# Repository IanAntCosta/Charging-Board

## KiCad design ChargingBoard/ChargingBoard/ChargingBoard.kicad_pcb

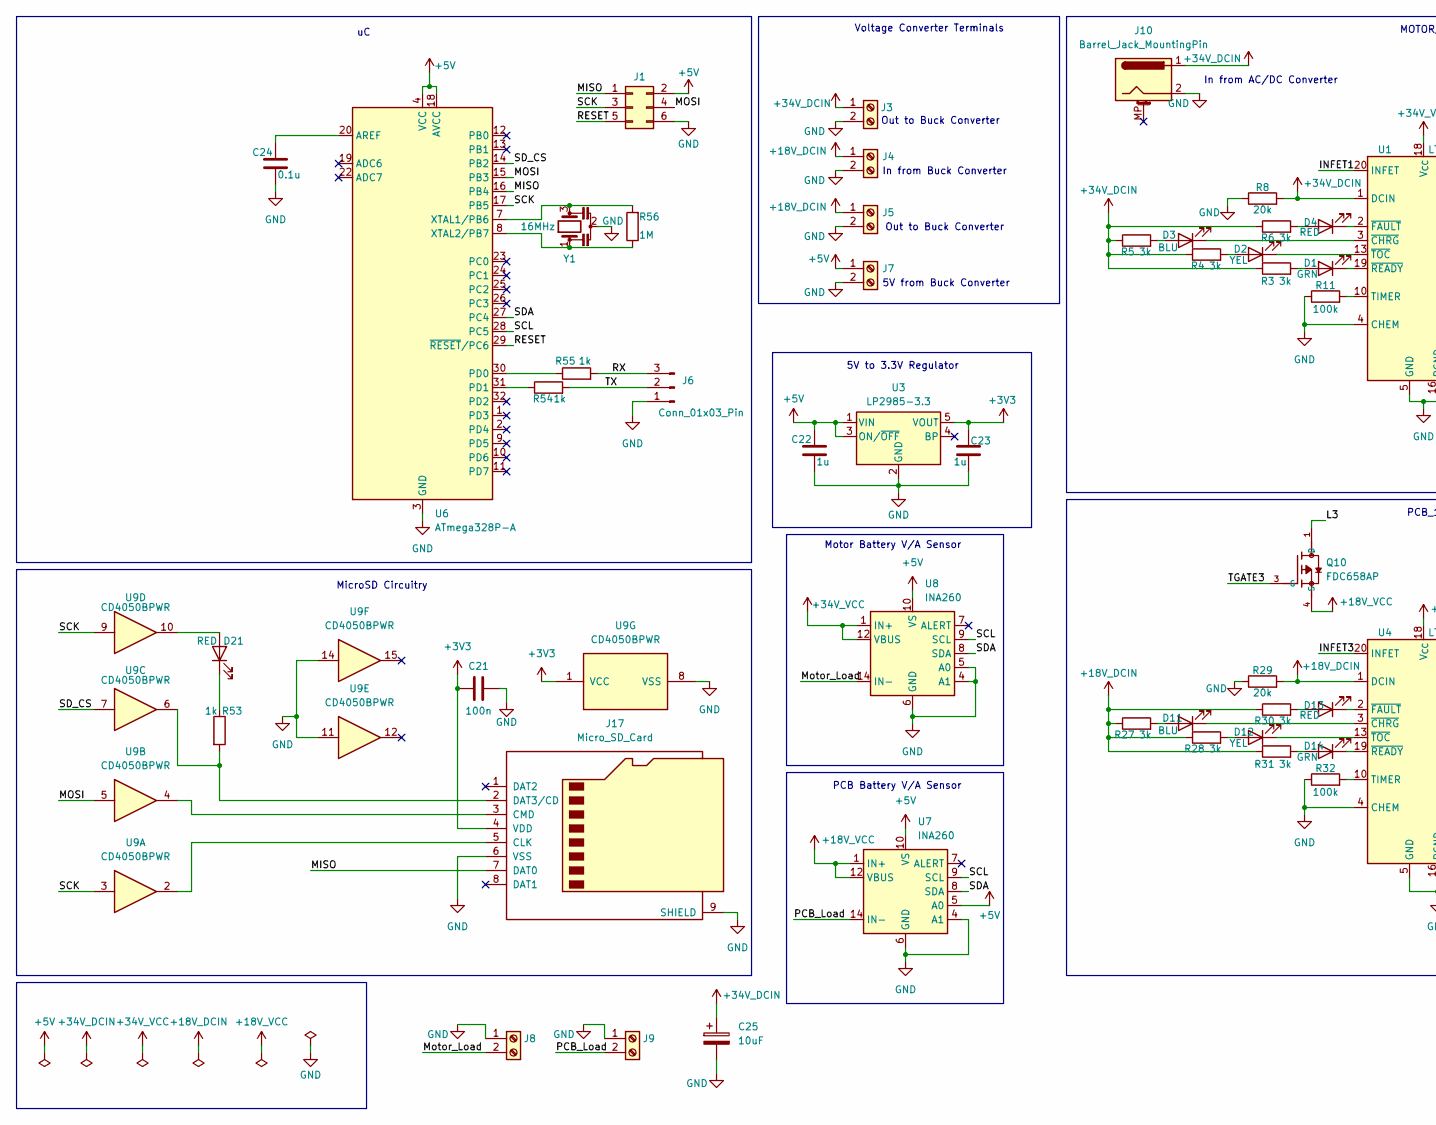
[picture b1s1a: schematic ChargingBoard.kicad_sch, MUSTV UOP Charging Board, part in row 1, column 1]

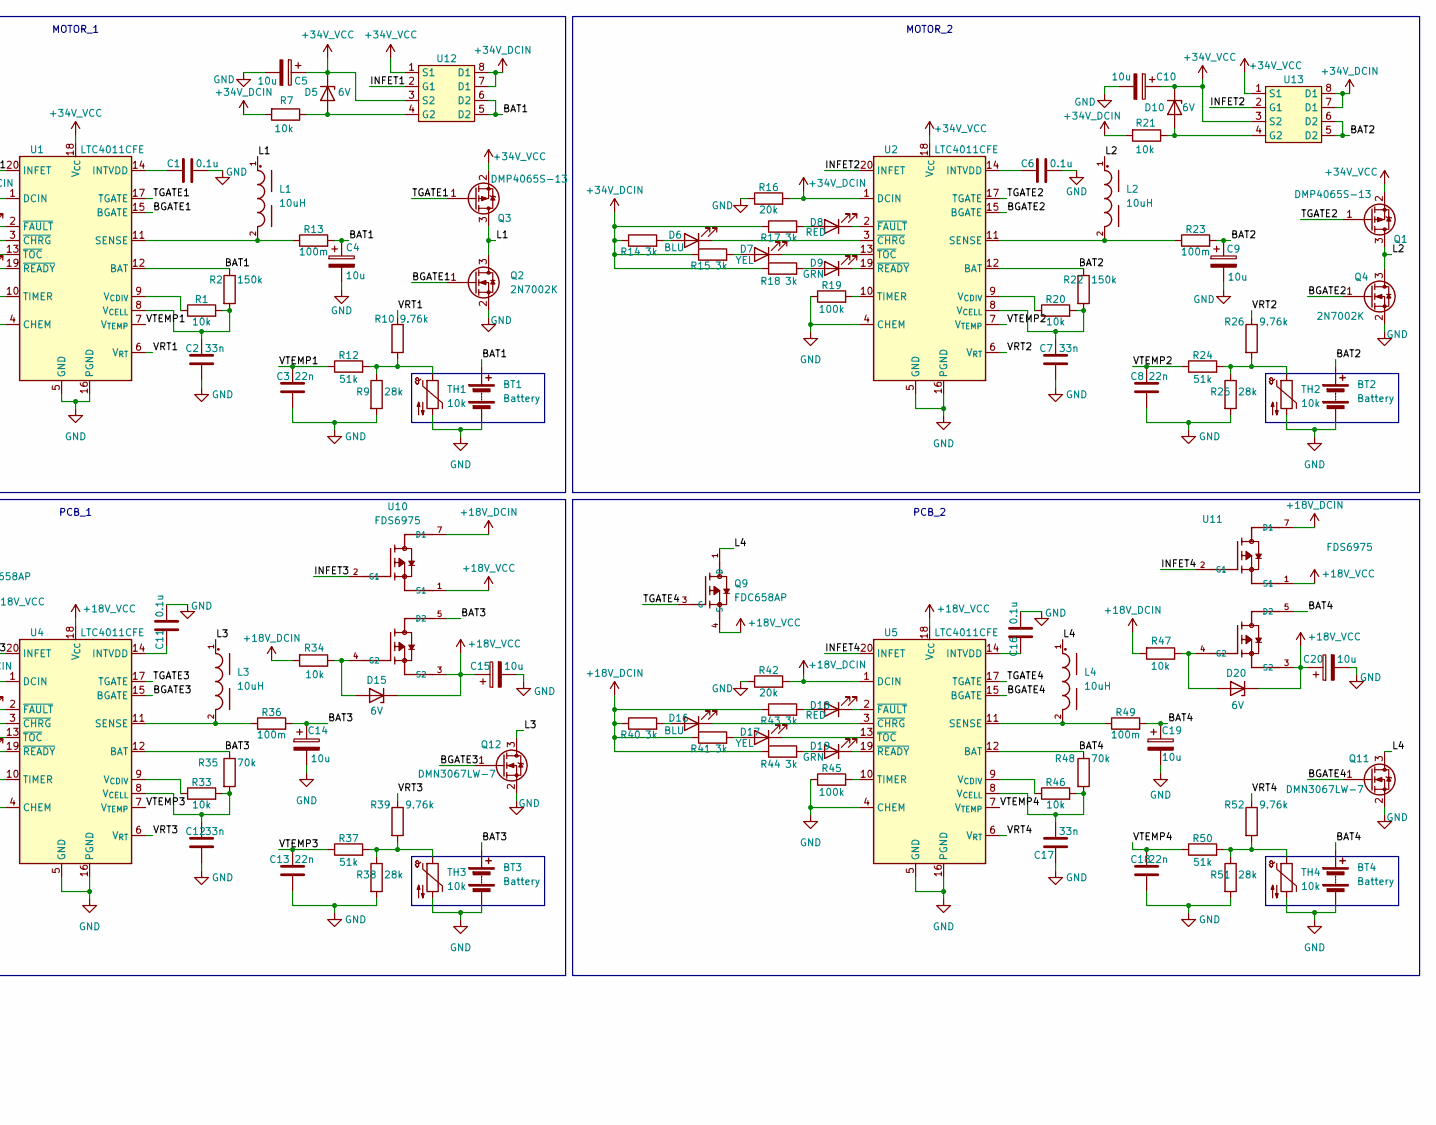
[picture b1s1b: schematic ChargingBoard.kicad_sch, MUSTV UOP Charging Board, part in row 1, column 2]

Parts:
BT1, BT2, BT3, BT4: Battery; TerminalBlock_Phoenix_MPT-0,5-2-2.54_1x02_P2.54mm_Horizontal
C1, C6, C11, C16, C24: 0.1u; C_0603_1608Metric_Pad1.08x0.95mm_HandSolder
C2, C7, C12, C17: 33n; C_0603_1608Metric_Pad1.08x0.95mm_HandSolder
C3, C8, C13, C18: 22n; C_0603_1608Metric_Pad1.08x0.95mm_HandSolder
C4, C5, C9, C10, C14, C15, C19, C20: 10u; CP_Radial_D5.0mm_P2.00mm
C21: 100n; C_0603_1608Metric_Pad1.08x0.95mm_HandSolder
C22, C23: 1u; C_0603_1608Metric_Pad1.08x0.95mm_HandSolder
C25: 10uF; CP_Axial_L10.0mm_D4.5mm_P15.00mm_Horizontal
D1, D9, D14, D19: GRN; LED_0603_1608Metric_Pad1.05x0.95mm_HandSolder
D2, D7, D12, D17: YEL; LED_0603_1608Metric_Pad1.05x0.95mm_HandSolder
D3, D6, D11, D16: BLU; LED_0603_1608Metric_Pad1.05x0.95mm_HandSolder
D4, D8, D13, D18, D21: RED; LED_0603_1608Metric_Pad1.05x0.95mm_HandSolder
D5, D10: 6V; D_SOD-123F
D15, D20: 6V; D_SOD-323_HandSoldering
J1: Conn_02x03_Odd_Even; PinSocket_2x03_P2.54mm_Vertical
J3, J4, J5, J7, J8, J9: Screw_Terminal_01x02; TerminalBlock_Phoenix_MKDS-1-2-3.81_1x02_P3.81mm_Horizontal
J6: Conn_01x03_Pin; PinHeader_1x03_P2.54mm_Vertical
J10: Barrel_Jack_MountingPin; BarrelJack_GCT_DCJ200-10-A_Horizontal
J17: Micro_SD_Card; microSD_HC_Hirose_DM3BT-DSF-PEJS
L1, L2, L3, L4: 10uH; WE-LHMI_7050; DigiKey_Part_Number 732-3358-1-ND
Q1, Q3: DMP4065S-13; SOT-23
Q2, Q4: 2N7002K; SOT-23
Q9, Q10: FDC658AP; SuperSOT-6
Q11, Q12: DMN3067LW-7; SOT-323_SC-70
R1, R7, R20, R21, R33, R34, R46, R47: 10k; R_0603_1608Metric_Pad0.98x0.95mm_HandSolder
R2, R22: 150k; R_0603_1608Metric_Pad0.98x0.95mm_HandSolder
R3, R4, R5, R6, R14, R15, R17, R18, R27, R28, R30, R31, R40, R41, R43, R44: 3k; R_0603_1608Metric_Pad0.98x0.95mm_HandSolder
R8, R16, R29, R42: 20k; R_0603_1608Metric_Pad0.98x0.95mm_HandSolder
R9, R25, R38, R51: 28k; R_0603_1608Metric_Pad0.98x0.95mm_HandSolder
R10, R26, R39, R52: 9.76k; R_0603_1608Metric_Pad0.98x0.95mm_HandSolder
R11, R19, R32, R45: 100k; R_0603_1608Metric_Pad0.98x0.95mm_HandSolder
R12, R24, R37, R50: 51k; R_0603_1608Metric_Pad0.98x0.95mm_HandSolder
R13, R23, R36, R49: 100m; R_0805_2012Metric_Pad1.20x1.40mm_HandSolder
R35, R48: 70k; R_0603_1608Metric_Pad0.98x0.95mm_HandSolder
R53, R54, R55: 1k; R_0603_1608Metric_Pad0.98x0.95mm_HandSolder
R56: 1M; R_0603_1608Metric_Pad0.98x0.95mm_HandSolder
TH1, TH2, TH3, TH4: 10k; PinHeader_1x02_P2.54mm_Vertical
U1, U2, U4, U5: LTC4011CFE; HTSSOP-20-1EP_4.4x6.5mm_P0.65mm_EP2.74x3.86mm
U3: LP2985-3.3; SOT-23-5
U6: ATmega328P-A; TQFP-32_7x7mm_P0.8mm
U7, U8: INA260; TSSOP-16_4.4x5mm_P0.65mm
U9: CD4050BPWR; SOIC-16_3.9x9.9mm_P1.27mm
U10, U11: FDS6975; SOIC-8_3.9x4.9mm_P1.27mm
U12, U13: Si4909DY-T1-GE3; SOIC-8_3.9x4.9mm_P1.27mm
Y1: 16MHz; Resonator_Murata_DSN6-3Pin_W7.0mm_H2.5mm

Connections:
+3V3: C21.1, C23.1, J17.4 (VDD), U3.5 (VOUT), U9.1 (VCC)
+5V: C22.1, J1.2, J7.1, U3.1 (VIN), U3.3 (ON/~OFF), U6.4 (VCC), U6.6 (VCC), U6.18 (AVCC), U7.5 (A0), U7.10 (VS), U8.10 (VS)
+18V_DCIN: J4.1, J5.1, R27.1, R28.1, R29.2, R30.1, R31.1, R34.2, R40.1, R41.1, R42.2, R43.1, R44.1, R47.2, U4.1 (DCIN), U5.1 (DCIN), U10.7 (D1), U10.8 (D1), U11.7 (D1), U11.8 (D1)
+18V_VCC: C15.1, C20.1, D15.1 (K), D20.1 (K), Q9.4 (S), Q10.4 (S), U4.18 (V_{CC}), U5.18 (V_{CC}), U7.1 (IN+), U7.2 (IN+), U7.3 (IN+), U7.12 (VBUS), U10.1 (S1), U10.3 (S2), U11.1 (S1), U11.3 (S2)
+34V_DCIN: C25.1, J3.1, J10.1, R3.1, R4.1, R5.1, R6.1, R7.2, R8.2, R14.1, R15.1, R16.2, R17.1, R18.1, R21.2, U1.1 (DCIN), U2.1 (DCIN), U12.7 (D1), U12.8 (D1), U13.7 (D1), U13.8 (D1)
+34V_VCC: C5.1, C10.1, D5.1 (K), D10.1 (K), Q1.2 (S), Q3.2 (S), U1.18 (V_{CC}), U2.18 (V_{CC}), U8.1 (IN+), U8.2 (IN+), U8.3 (IN+), U8.12 (VBUS), U12.1 (S1), U12.3 (S2), U13.1 (S1), U13.3 (S2)
/BAT1: BT1.1 (+), C4.1, R2.1, R13.2, U1.12 (BAT), U12.5 (D2), U12.6 (D2)
/BAT2: BT2.1 (+), C9.1, R22.1, R23.2, U2.12 (BAT), U13.5 (D2), U13.6 (D2)
/BAT3: BT3.1 (+), C14.1, R35.1, R36.2, U4.12 (BAT), U10.5 (D2), U10.6 (D2)
/BAT4: BT4.1 (+), C19.1, R48.1, R49.2, U5.12 (BAT), U11.5 (D2), U11.6 (D2)
/BGATE1: Q2.1 (G), U1.15 (BGATE)
/BGATE2: Q4.1 (G), U2.15 (BGATE)
/BGATE3: Q12.1 (G), U4.15 (BGATE)
/BGATE4: Q11.1 (G), U5.15 (BGATE)
/INFET1: U1.20 (INFET), U12.2 (G1)
/INFET2: U2.20 (INFET), U13.2 (G1)
/INFET3: U4.20 (INFET), U10.2 (G1)
/INFET4: U5.20 (INFET), U11.2 (G1)
/L1: L1.1, Q2.3 (D), Q3.3 (D)
/L2: L2.1, Q1.3 (D), Q4.3 (D)
/L3: L3.1, Q10.1 (D), Q10.2 (D), Q10.5 (D), Q10.6 (D), Q12.3 (D)
/L4: L4.1, Q9.1 (D), Q9.2 (D), Q9.5 (D), Q9.6 (D), Q11.3 (D)
/MISO: J1.1, J17.7 (DAT0), U6.16 (PB4)
/MOSI: J1.4, U6.15 (PB3), U9.5
/Motor_Load: J8.2, U8.14 (IN-), U8.15 (IN-), U8.16 (IN-)
/PCB_Load: J9.2, U7.14 (IN-), U7.15 (IN-), U7.16 (IN-)
/RESET: J1.5, U6.29 (~RESET/PC6)
/RX: J6.3, R55.2
/SCK: J1.3, U6.17 (PB5), U9.3, U9.9
/SCL: U6.28 (PC5), U7.9 (SCL), U8.9 (SCL)
/SDA: U6.27 (PC4), U7.8 (SDA), U8.8 (SDA)
/SD_CS: U6.14 (PB2), U9.7
/TGATE1: Q3.1 (G), U1.17 (TGATE)
/TGATE2: Q1.1 (G), U2.17 (TGATE)
/TGATE3: Q10.3 (G), U4.17 (TGATE)
/TGATE4: Q9.3 (G), U5.17 (TGATE)
/TX: J6.2, R54.2
/VRT1: R10.1, U1.6 (V_{RT})
/VRT2: R26.1, U2.6 (V_{RT})
/VRT3: R39.1, U4.6 (V_{RT})
/VRT4: R52.1, U5.6 (V_{RT})
/VTEMP1: C3.1, R12.1, U1.7 (V_{TEMP})
/VTEMP2: C8.1, R24.1, U2.7 (V_{TEMP})
/VTEMP3: C13.1, R37.1, U4.7 (V_{TEMP})
/VTEMP4: C18.1, R50.1, U5.7 (V_{TEMP})
GND: BT1.2 (-), BT2.2 (-), BT3.2 (-), BT4.2 (-), C1.2, C2.2, C3.2, C4.2, C5.2, C6.2, C7.2, C8.2, C9.2, C10.2, C11.2, C12.2, C13.2, C14.2, C15.2, C16.2, C17.2, C18.2, C19.2, C20.2, C21.2, C22.2, C23.2, C24.2, C25.2, J1.6, J3.2, J4.2, J5.2, J6.1, J7.2, J8.1, J9.1, J10.2, J17.6 (VSS), J17.9 (SHIELD), Q2.2 (S), Q4.2 (S), Q11.2 (S), Q12.2 (S), R8.1, R9.2, R11.1, R16.1, R19.1, R25.2, R29.1, R32.1, R38.2, R42.1, R45.1, R51.2, TH1.2, TH2.2, TH3.2, TH4.2, U1.4 (CHEM), U1.5 (GND), U1.16 (PGND), U1.21 (GND), U2.4 (CHEM), U2.5 (GND), U2.16 (PGND), U2.21 (GND), U3.2 (GND), U4.4 (CHEM), U4.5 (GND), U4.16 (PGND), U4.21 (GND), U5.4 (CHEM), U5.5 (GND), U5.16 (PGND), U5.21 (GND), U6.3 (GND), U6.5 (GND), U6.21 (GND), U7.4 (A1), U7.6 (GND), U7.11 (GND), U8.4 (A1), U8.5 (A0), U8.6 (GND), U8.11 (GND), U9.8 (VSS), U9.11, U9.14, Y1.2
unnamed: D1.2 (A), R3.2
unnamed: D1.1 (K), U1.19 (~READY)
unnamed: D2.2 (A), R4.2
unnamed: D2.1 (K), U1.13 (~TOC)
unnamed: D3.2 (A), R5.2
unnamed: D3.1 (K), U1.3 (~CHRG)
unnamed: D4.2 (A), R6.2
unnamed: D4.1 (K), U1.2 (~FAULT)
unnamed: D5.2 (A), R7.1, U12.4 (G2)
unnamed: D6.2 (A), R14.2
unnamed: D6.1 (K), U2.3 (~CHRG)
unnamed: D7.2 (A), R15.2
unnamed: D7.1 (K), U2.13 (~TOC)
unnamed: D8.2 (A), R17.2
unnamed: D8.1 (K), U2.2 (~FAULT)
unnamed: D9.2 (A), R18.2
unnamed: D9.1 (K), U2.19 (~READY)
unnamed: D10.2 (A), R21.1, U13.4 (G2)
unnamed: D11.2 (A), R27.2
unnamed: D11.1 (K), U4.3 (~CHRG)
unnamed: D12.2 (A), R28.2
unnamed: D12.1 (K), U4.13 (~TOC)
unnamed: D13.2 (A), R30.2
unnamed: D13.1 (K), U4.2 (~FAULT)
unnamed: D14.2 (A), R31.2
unnamed: D14.1 (K), U4.19 (~READY)
unnamed: D15.2 (A), R34.1, U10.4 (G2)
unnamed: D16.2 (A), R40.2
unnamed: D16.1 (K), U5.3 (~CHRG)
unnamed: D17.2 (A), R41.2
unnamed: D17.1 (K), U5.13 (~TOC)
unnamed: D18.2 (A), R43.2
unnamed: D18.1 (K), U5.2 (~FAULT)
unnamed: D19.2 (A), R44.2
unnamed: D19.1 (K), U5.19 (~READY)
unnamed: D20.2 (A), R47.1, U11.4 (G2)
unnamed: D21.2 (A), U9.10
unnamed: D21.1 (K), R53.1
unnamed: J17.5 (CLK), U9.2
unnamed: J17.3 (CMD), U9.4
unnamed: J17.2 (DAT3/CD), R53.2, U9.6
unnamed: R9.1, R10.2, R12.2, TH1.1
unnamed: R24.2, R25.1, R26.2, TH2.1
unnamed: R37.2, R38.1, R39.2, TH3.1
unnamed: R50.2, R51.1, R52.2, TH4.1
unnamed: C1.1, U1.14 (INTVDD)
unnamed: L1.2, R13.1, U1.11 (SENSE)
unnamed: R11.2, U1.10 (TIMER)
unnamed: R1.1, U1.9 (V_{CDIV})
unnamed: C2.1, R1.2, R2.2, U1.8 (V_{CELL})
unnamed: C6.1, U2.14 (INTVDD)
unnamed: L2.2, R23.1, U2.11 (SENSE)
unnamed: R19.2, U2.10 (TIMER)
unnamed: R20.1, U2.9 (V_{CDIV})
unnamed: C7.1, R20.2, R22.2, U2.8 (V_{CELL})
unnamed: C11.1, U4.14 (INTVDD)
unnamed: L3.2, R36.1, U4.11 (SENSE)
unnamed: R32.2, U4.10 (TIMER)
unnamed: R33.1, U4.9 (V_{CDIV})
unnamed: C12.1, R33.2, R35.2, U4.8 (V_{CELL})
unnamed: C16.1, U5.14 (INTVDD)
unnamed: L4.2, R49.1, U5.11 (SENSE)
unnamed: R45.2, U5.10 (TIMER)
unnamed: R46.1, U5.9 (V_{CDIV})
unnamed: C17.1, R46.2, R48.2, U5.8 (V_{CELL})
unnamed: C24.1, U6.20 (AREF)
unnamed: R55.1, U6.30 (PD0)
unnamed: R54.1, U6.31 (PD1)
unnamed: R56.2, U6.7 (XTAL1/PB6), Y1.3
unnamed: R56.1, U6.8 (XTAL2/PB7), Y1.1

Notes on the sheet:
MOTOR_2
MicroSD Circuitry
Voltage Converter Terminals
PCB_2
In from Buck Converter
PCB_1
PCB Battery V/A Sensor
Out to Buck Converter
In from AC/DC Converter
Motor Battery V/A Sensor
5V from Buck Converter
5V to 3.3V Regulator
MOTOR_1

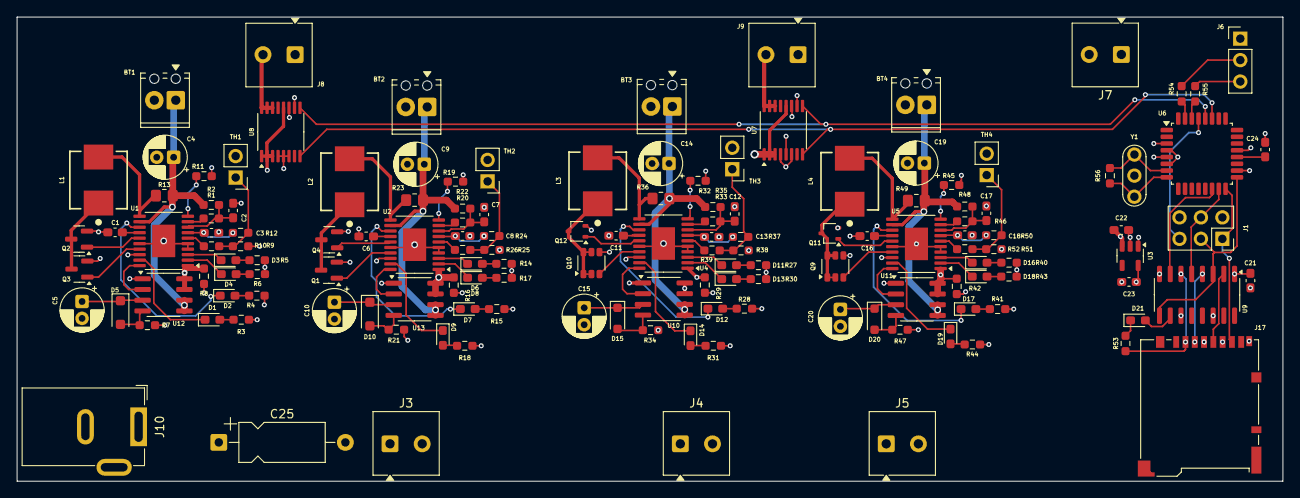
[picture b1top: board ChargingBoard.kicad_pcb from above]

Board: 4 copper layers, 150.0 x 55.0 mm, 146 parts (0 on the bottom side), 116 nets.

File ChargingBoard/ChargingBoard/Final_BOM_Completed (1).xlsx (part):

Reference | Qty | Value | DNP | Exclude from BOM | Exclude from Board | Footprint | Datasheet | Case Code | Source | Unit Cost ($) | Total Cost ($) | Manufacturer | Mouser Part # | Link
BT1,BT2,BT3,BT4 | 4 | Battery |  |  |  | TerminalBlock_Phoenix:TerminalBlock_Phoenix_MPT-0,5-2-2.54_1x02_P2.54mm_Horizon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 | ~ |  | Mouser
C1,C6,C11,C16,C24 | 5 | 0.1u |  |  |  | Capacitor_SMD:C_0603_1608Metric_Pad1.08x0.95mm_HandSolder | https://ds.yuden.co.jp/TYCOMPAS/or/download?pn=MBARQ167SCG0R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 | 1608 | Mouser | 0.16 | 0.8 | Taiyo Yuden | 963-BASH168SB7104KT | https://www.mouser.com/ProductDetail/TAIYO-YUDEN/MBASH168SB7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
C2,C7,C12,C17 | 4 | 33n |  |  |  | Capacitor_SMD:C_0603_1608Metric_Pad1.08x0.95mm_HandSolder | https://product.tdk.com/system/files/dam/doc/product/capacit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 | 1608 | Mouser | 0.21 | 0.84 | TDK | 810-C1608X8R2A333KAB | https://www.mouser.com/ProductDetail/TDK/C1608X8R2A333K080AB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
C3,C8,C13,C18 | 4 | 22n |  |  |  | Capacitor_SMD:C_0603_1608Metric_Pad1.08x0.95mm_HandSolder | https://product.tdk.com/system/files/dam/doc/product/capacit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 | 1608 | Mouser | 0.14000000000000001 | 0.56000000000000005 | TDK | 810-C1608X8R1H223M0A | https://www.mouser.com/ProductDetail/TDK/C1608X8R1H223M080AA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
C4,C5,C9,C10,C14,C15,C19,C20 | 8 | 10u |  |  |  | Capacitor_THT:CP_Radial_D5.0mm_P2.00mm | https://product.tdk.com/system/files/dam/doc/product/capacit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 | 1608 | Mouser | 0.22 | 1.76 | TDK | 810-C1608X7R1A106M08 | https://www.mouser.com/ProductDetail/TDK/C1608X7R1A106M080AT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
C21 | 1 | 100n |  |  |  | Capacitor_SMD:C_0603_1608Metric_Pad1.08x0.95mm_HandSolder | https://product.tdk.com/system/files/dam/doc/product/capacit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 | 1608 | Mouser | 0.2 | 0.2 | TDK | 810-C1608X8R1H104K | https://www.mouser.com/ProductDetail/TDK/C1608X8R1H104K080AA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
C22,C23 | 2 | 1u |  |  |  | Capacitor_SMD:C_0603_1608Metric_Pad1.08x0.95mm_HandSolder | https://www.mouser.com/datasheet/3/940/1/c_mlcc_S_e.pdf | 1608 | Mouser | 0.1 | 0.2 | Yuden | 963-MSASE168SB5105KT | https://www.mouser.com/ProductDetail/TAIYO-YUDEN/MSASE168SB5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
C25 | 1 | 10uF |  |  |  | Capacitor_THT:CP_Axial_L10.0mm_D4.5mm_P15.00mm_Horizontal | https://product.tdk.com/system/files/dam/doc/product/capacit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 | 1608 | Mouser | 0.22 | 0.22 | TDK | 810-C1608X7R1A106M08 | https://www.mouser.com/ProductDetail/TDK/C1608X7R1A106M080AT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
D1,D9,D14,D19 | 4 | GRN |  |  |  | LED_SMD:LED_0603_1608Metric_Pad1.05x0.95mm_HandSolder | ~ |  | Mouser
D2,D7,D12,D17 | 4 | YEL |  |  |  | LED_SMD:LED_0603_1608Metric_Pad1.05x0.95mm_HandSolder | ~ |  | Mouser
D3,D6,D11,D16 | 4 | BLU |  |  |  | LED_SMD:LED_0603_1608Metric_Pad1.05x0.95mm_HandSolder | ~ |  | Mouser
D4,D8,D13,D18,D21 | 5 | RED |  |  |  | LED_SMD:LED_0603_1608Metric_Pad1.05x0.95mm_HandSolder | ~ |  | Mouser
D5,D10 | 2 | 6V |  |  |  | Diode_SMD:D_SOD-123F | https://www.vishay.com/docs/85816/1n4728a.pdf |  | Mouser
D15,D20 | 2 | 6V |  |  |  | Diode_SMD:D_SOD-323_HandSoldering | https://www.vishay.com/docs/85816/1n4728a.pdf |  | Mouser
J1 | 1 | Conn_02x03_Odd_Even |  |  |  | Connector_PinSocket_2.54mm:PinSocket_2x03_P2.54mm_Vertical | ~ |  | Mouser
J3,J4,J5,J7,J8,J9 | 6 | Screw_Terminal_01x02 |  |  |  | TerminalBlock_Phoenix:TerminalBlock_Phoenix_MKDS-1-2-3.81_1x02_P3.81mm_Horizont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 | ~ |  | Mouser
J6 | 1 | Conn_01x03_Pin |  |  |  | Connector_PinHeader_2.54mm:PinHeader_1x03_P2.54mm_Vertical | ~ |  | Mouser
J10 | 1 | Barrel_Jack_MountingPin |  |  |  | Connector_BarrelJack:BarrelJack_GCT_DCJ200-10-A_Horizontal | ~ |  | Mouser
J17 | 1 | Micro_SD_Card |  |  |  | Connector_Card:microSD_HC_Hirose_DM3BT-DSF-PEJS | https://www.we-online.com/components/products/datasheet/6930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 |  | Mouser
L1,L2,L3,L4 | 4 | 10uH |  |  |  | WE-LHMI_7050:WE-LHMI_7050 |  |  | Mouser
Q1,Q3 | 2 | DMP4065S-13 |  |  |  | Package_TO_SOT_SMD:SOT-23 | https://www.onsemi.com/pub/Collateral/FQP27P06-D.PDF |  | Mouser
Q2,Q4 | 2 | 2N7002K |  |  |  | Package_TO_SOT_SMD:SOT-23 | https://www.diodes.com/assets/Datasheets/ds30896.pdf |  | Mouser
Q9,Q10 | 2 | FDC658AP |  |  |  | Package_TO_SOT_SMD:SuperSOT-6 |  |  | Mouser
Q11,Q12 | 2 | DMN3067LW-7 |  |  |  | Package_TO_SOT_SMD:SOT-323_SC-70 | http://www.irf.com/product-info/datasheets/data/irlz44n.pdf |  | Mouser
R1,R7,R20,R21,R33,R34,R46,R47 | 8 | 10k |  |  |  | Resistor_SMD:R_0603_1608Metric_Pad0.98x0.95mm_HandSolder | https://www.mouser.com/datasheet/3/826/1/n_catalog_partition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 | 1608 | Mouser | 0.1 | 0.8 | Susumu | 754-RG1608P-103-B-T5 | https://www.mouser.com/ProductDetail/Susumu/RG1608P-103-B-T5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
R2,R22 | 2 | 150k |  |  |  | Resistor_SMD:R_0603_1608Metric_Pad0.98x0.95mm_HandSolder | https://www.mouser.com/datasheet/3/826/1/n_catalog_partition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 | 1608 | Mouser | 0.1 | 0.2 | Susumu | 754-RG1608P-154-B-T5 | https://www.mouser.com/ProductDetail/Susumu/RG1608P-154-B-T5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
R3,R4,R5,R6,R14,R15,R17,R18,R27,R28,R30,R31,R40,R41,R43,R44 | 16 | 3k |  |  |  | Resistor_SMD:R_0603_1608Metric_Pad0.98x0.95mm_HandSolder | https://www.mouser.com/datasheet/3/826/1/n_catalog_partition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 | 1608 | Mouser | 0.1 | 1.6 | Susumu | 754-RG1608P-302-B-T5 | https://www.mouser.com/ProductDetail/Susumu/RG1608P-302-B-T5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
R8,R16,R29,R42 | 4 | 20k |  |  |  | Resistor_SMD:R_0603_1608Metric_Pad0.98x0.95mm_HandSolder | https://www.mouser.com/datasheet/3/826/1/n_catalog_partition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 | 1608 | Mouser | 0.1 | 0.4 | Susumu | 754-RG1608P-203-B-T5 | https://www.mouser.com/ProductDetail/Susumu/RG1608P-203-B-T5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
R9,R25,R38,R51 | 4 | 28k |  |  |  | Resistor_SMD:R_0603_1608Metric_Pad0.98x0.95mm_HandSolder | https://www.mouser.com/datasheet/3/826/1/n_catalog_partition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 | 1608 | Mouser | 0.12 | 0.48 | Susumu | 754-RG1608P-2802-BT5 | https://www.mouser.com/ProductDetail/Susumu/RG1608P-2802-B-T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
R10,R26,R39,R52 | 4 | 9.76k |  |  |  | Resistor_SMD:R_0603_1608Metric_Pad0.98x0.95mm_HandSolder | https://www.mouser.com/datasheet/3/826/1/n_catalog_partition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 | 1608 | Mouser | 0.36 | 1.44 | Susumu | 754-RGT1608P9761BT5 | https://www.mouser.com/ProductDetail/Susumu/RGT1608P-9761-B-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
R11,R19,R32,R45 | 4 | 100k |  |  |  | Resistor_SMD:R_0603_1608Metric_Pad0.98x0.95mm_HandSolder | https://www.mouser.com/datasheet/3/826/1/n_catalog_partition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 | 1608 | Mouser | 0.1 | 0.4 | Susumu | 754-RG1608P-104-B-T5 | https://www.mouser.com/ProductDetail/Susumu/RG1608P-104-B-T5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
R12,R24,R37,R50 | 4 | 51k |  |  |  | Resistor_SMD:R_0603_1608Metric_Pad0.98x0.95mm_HandSolder | https://www.mouser.com/datasheet/3/826/1/n_catalog_partition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 | 1608 | Mouser | 0.12 | 0.48 | Susumu | 754-RG1608P-513-BT5 | https://www.mouser.com/ProductDetail/Susumu/RG1608P-513-B-T5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
R13,R23,R36,R49 | 4 | 100m |  |  |  | Resistor_SMD:R_0805_2012Metric_Pad1.20x1.40mm_HandSolder |  | 2012 | Mouser
R35,R48 | 2 | 70k |  |  |  | Resistor_SMD:R_0603_1608Metric_Pad0.98x0.95mm_HandSolder |  | 1608 | Mouser
R53,R54,R55 | 3 | 1k |  |  |  | Resistor_SMD:R_0603_1608Metric_Pad0.98x0.95mm_HandSolder | https://www.mouser.com/datasheet/3/826/1/n_catalog_partition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 | 1608 | Mouser | 0.1 | 0.3 | Susumu | 754-RG1608P-102-B-T5 | https://www.mouser.com/ProductDetail/Susumu/RG1608P-102-B-T5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
R56 | 1 | 1M |  |  |  | Resistor_SMD:R_0603_1608Metric_Pad0.98x0.95mm_HandSolder | https://www.mouser.com/datasheet/3/826/1/n_catalog_partition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 | 1608 | Mouser | 0.36 | 0.36 | Susumu | 754-RGT1608P-105BT5 | https://www.mouser.com/ProductDetail/Susumu/RGT1608P-105-B-T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
TH1,TH2,TH3,TH4 | 4 | 10k |  |  |  | Connector_PinHeader_2.54mm:PinHeader_1x02_P2.54mm_Vertical |  |  | Mouser
U1,U2,U4,U5 | 4 | LTC4011CFE |  |  |  | Package_SO:HTSSOP-20-1EP_4.4x6.5mm_P0.65mm_EP2.74x3.86mm | https://www.analog.com/media/en/technical-documentation/data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 | Package_SO:HTSSOP-20-1EP_4.4x6.5mm_P0.65mm_EP2.74x3.86mm | Mouser | 13.99 | 55.96 | Analog Devices | 584-LTC4011CFE#PBF | https://www.mouser.com/ProductDetail/Analog-Devices/LTC4011EUF-PBF
U3 | 1 | LP2985-3.3 |  |  |  | Package_TO_SOT_SMD:SOT-23-5 | http://www.ti.com/lit/ds/symlink/lp2985.pdf | Package_TO_SOT_SMD:SOT-23-5 | Mouser | 1.88 | 1.88 | Texas Instruments | 595-LP2985-18DBVRE4 | https://www.mouser.com/ProductDetail/Texas-Instruments/LP298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

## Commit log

2026-02-11 Initial commit - Senior Design Charging Board
2026-04-03 Integration
    Added charging circuits to project schematic, deleted redundant schematics
2026-04-03 SD Card and Voltage Conversion
    Swapped out microcontroller, added SD card circuit and conversion terminals for voltages, added 5V to 3.3V regulator
2026-04-17 junk
2026-04-17 dfbzfb
2026-04-18 Voltage Sensors Added
2026-04-19 Fixed Power Flags
2026-04-20 Component Reworks
    Changed MOSFET component footprints, diodes, etc.
2026-04-20 Arrangement Begins
2026-04-20 More Arranging
2026-04-21 MOSFETs changed
2026-04-21 Board Done
2026-04-21 Finishing Touches
